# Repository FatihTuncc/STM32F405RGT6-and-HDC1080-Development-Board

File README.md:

# _STM32F405RGT6 and HDC1080 Development Board_

In this project, a development board was designed using the STM32F405RGT6 processor, HDC1080 sensor and MP2359 step-down IC.
> [!NOTE]
> I rendered the PCB 3D file by transferring it to the Blender program and obtained this realistic image.
## _Components_

- **_STM32F405RGT6:_** The STM32F405RGT6 processor is ideal for high-performance embedded system applications with its 168 MHz processing speed and large memory capacity. I also chose this Microprocessor because it is affordable and new generation.

- **_HDC1080:_** The HDC1080 sensor provides high accuracy for temperature and humidity measurements. It works integrated with STM32F405RGT6 to provide accurate and reliable data. It can communicate with I2C Protocol. There may be alternatives instead of this sensor.

- **_MP2359:_** The MP2359 IC has a wide input voltage range. It saves energy with high efficiency Step-Down regulation. It is a well-known and widely used component.

> [!IMPORTANT]
> I designed the circuit design of these components in accordance with the datasheet. I drew the PCB Designs again in accordance with the Datasheet.

## _Components Recommended For Use (JLCPCB)_

- C13738 Crystal Oscillator
- C221841 Boot switch
- C408412 Power Inductor
- C132560 USB Connector

This information is also available in the BOM file.
## _PCB Image_

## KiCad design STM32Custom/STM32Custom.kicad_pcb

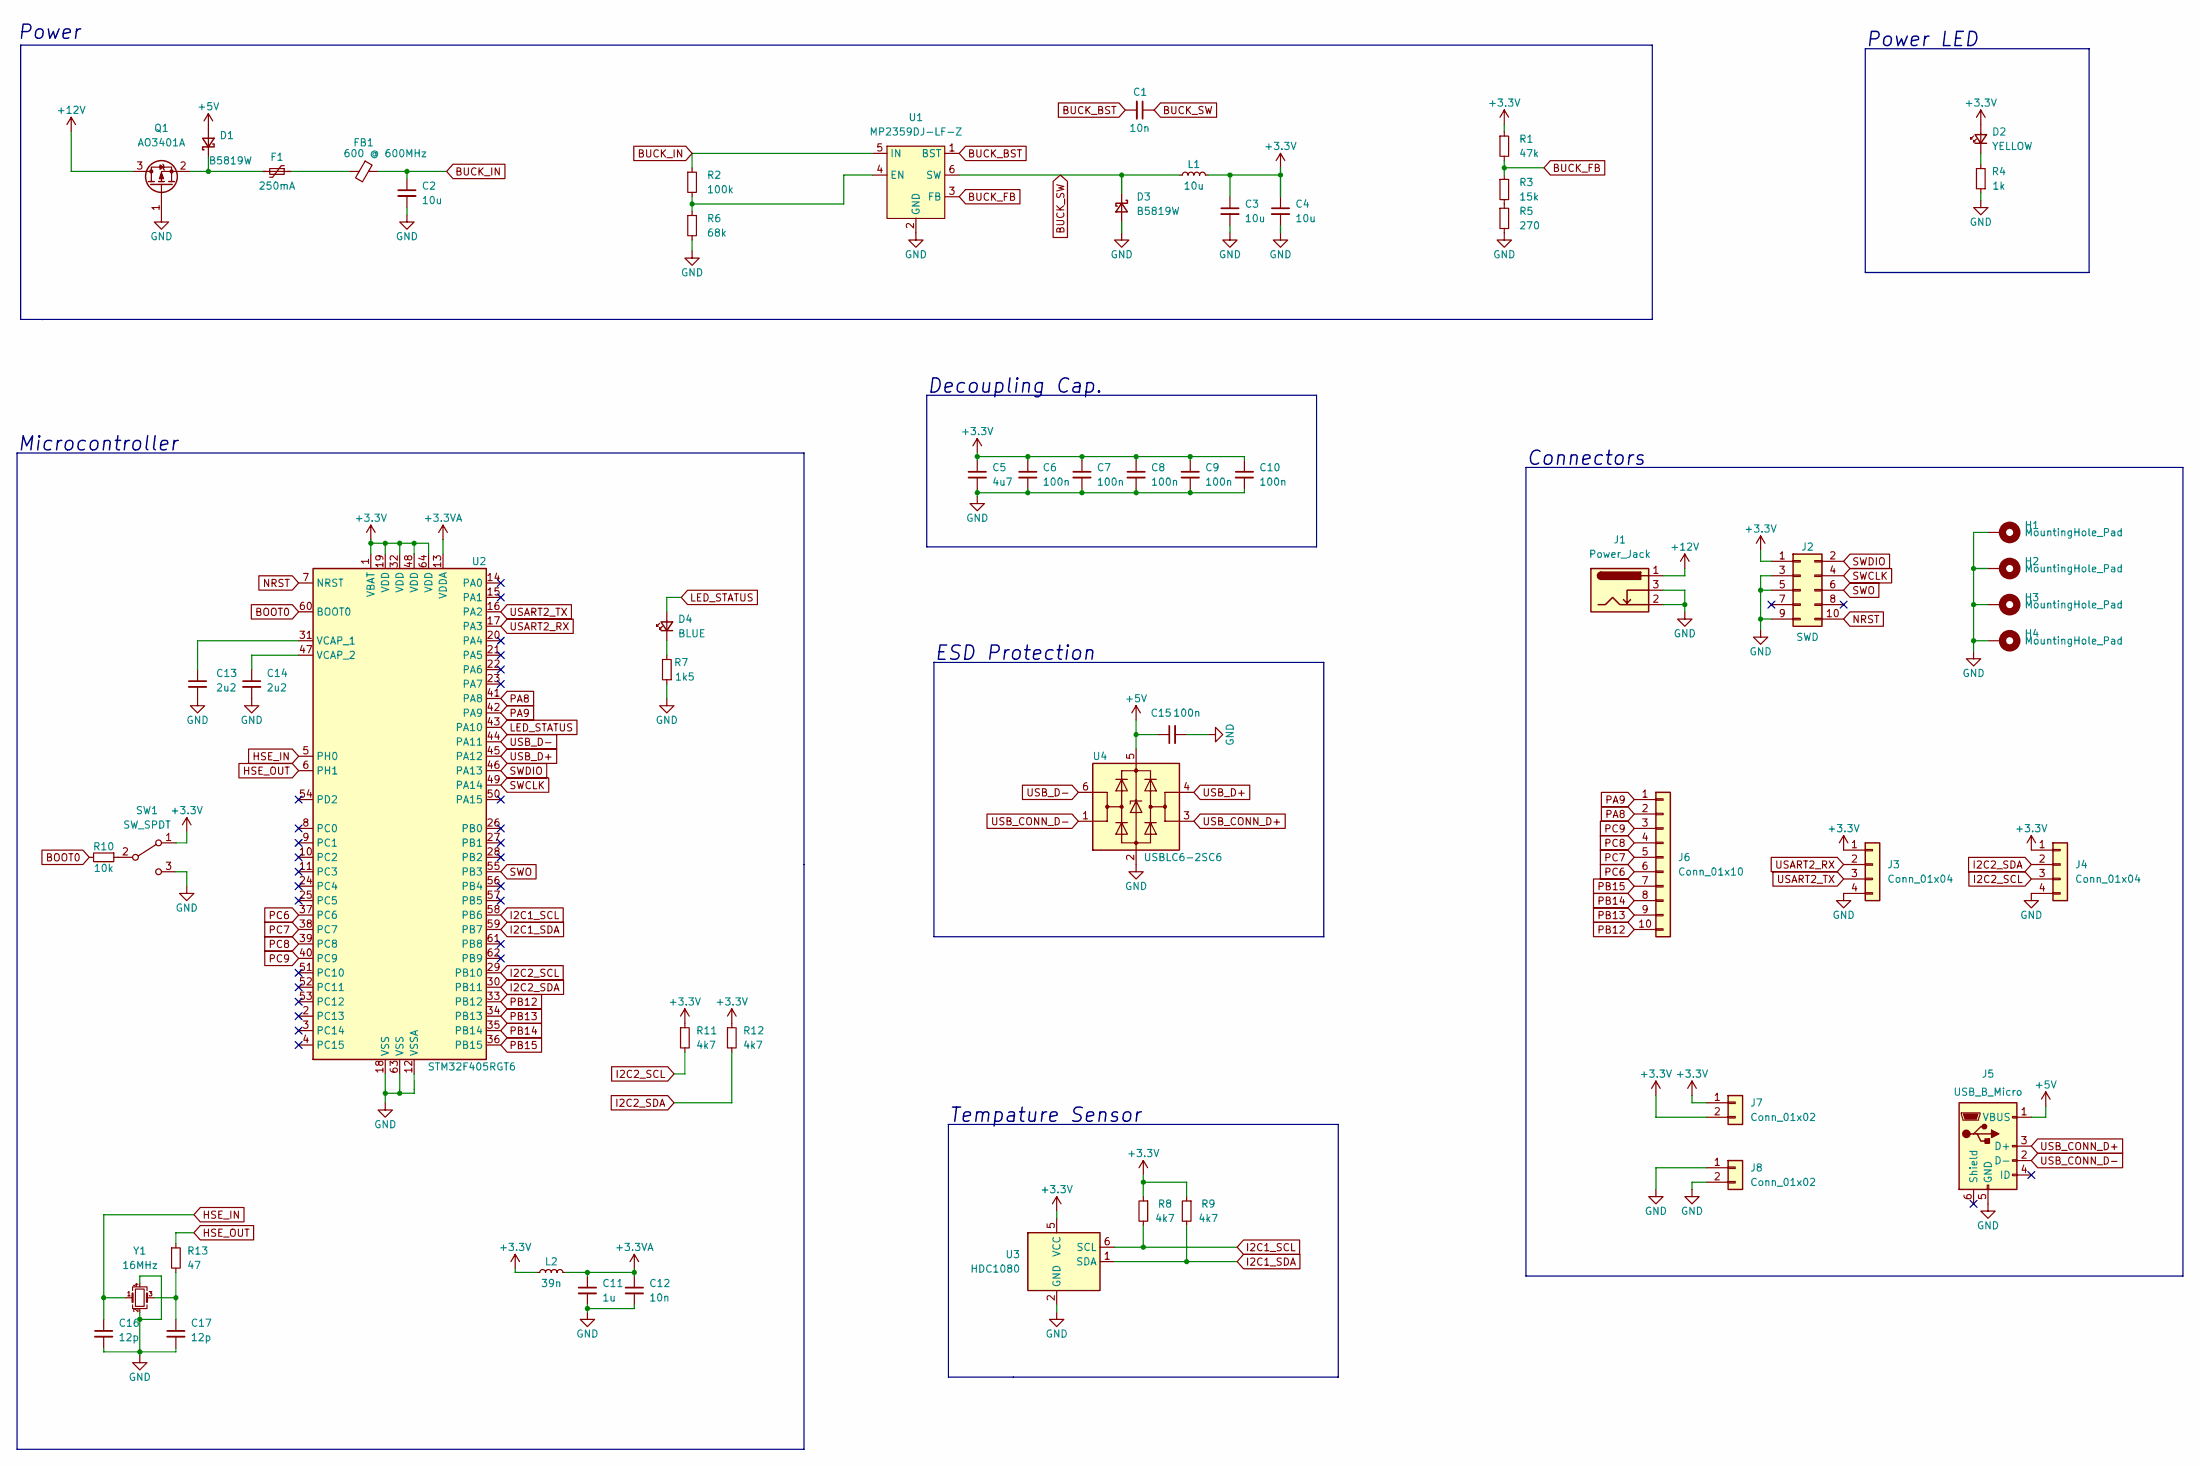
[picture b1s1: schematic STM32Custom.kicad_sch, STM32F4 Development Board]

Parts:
C1: 10n; C_0805_2012Metric; LCSC Part # C1710
C2, C3, C4: 10u; C_1206_3216Metric; LCSC Part # C13585
C5: 4u7; C_0805_2012Metric; LCSC Part # C1779
C6, C7, C8, C9, C10, C15: 100n; C_0603_1608Metric; LCSC Part # C14663
C11: 1u; C_0603_1608Metric; LCSC Part # C15849
C12: 10n; C_0603_1608Metric; LCSC Part # C57112
C13, C14: 2u2; C_0603_1608Metric; LCSC Part # C23630
C16, C17: 12p; C_0603_1608Metric; LCSC Part # C38523
D1, D3: B5819W; D_SOD-123; LCSC Part # C8598
D2: YELLOW; LED_0603_1608Metric; LCSC Part # C72038
D4: BLUE; LED_0603_1608Metric; LCSC Part # C72041
F1: 250mA; Fuse_1206_3216Metric; LCSC Part # C369159
FB1: 600 @ 600MHz; L_0805_2012Metric; LCSC Part # C1017
H1, H2, H3, H4: MountingHole_Pad; MountingHole_4.3mm_M4_Pad_Via
J1: Power_Jack; BarrelJack_Horizontal
J2: SWD; PinHeader_2x05_P2.54mm_Vertical
J3, J4: Conn_01x04; PinHeader_1x04_P2.54mm_Vertical
J5: USB_B_Micro; USB_Micro-B_Molex_47346-0001; LCSC Part # C132560
J6: Conn_01x10; PinHeader_1x10_P2.54mm_Vertical
J7, J8: Conn_01x02; PinHeader_1x02_P2.54mm_Vertical
L1: 10u; L_Sunlord_MWSA05xxS; LCSC Part # C408412
L2: 39n; L_0402_1005Metric; LCSC Part # C26443
Q1: AO3401A; SOT-23; LCSC Part # C15127
R1: 47k; R_0805_2012Metric; LCSC Part # C17713
R2: 100k; R_0805_2012Metric; LCSC Part # C149504
R3: 15k; R_0805_2012Metric; LCSC Part # C17475
R4: 1k; R_0805_2012Metric; LCSC Part # C17513
R5: 270; R_0805_2012Metric; LCSC Part # C17590
R6: 68k; R_0805_2012Metric; LCSC Part # C17801
R7: 1k5; R_0805_2012Metric; LCSC Part # C4310
R8, R9, R11, R12: 4k7; R_0805_2012Metric; LCSC Part # C17673
R10: 10k; R_0805_2012Metric; LCSC Part # C17414
R13: 47; R_0805_2012Metric; LCSC Part # C17714
SW1: SW_SPDT; SW_SPDT_PCM12; LCSC Part # C221841
U1: MP2359DJ-LF-Z; TSOT-23-6; LCSC Part # C2959845
U2: STM32F405RGT6; LQFP-64_10x10mm_P0.5mm; LCSC Part # C15742
U3: HDC1080; Texas_PWSON-N6; LCSC Part # C82227
U4: USBLC6-2SC6; SOT-23-6; LCSC Part # C7519
Y1: 16MHz; Crystal_SMD_3225-4Pin_3.2x2.5mm; LCSC Part # C13738

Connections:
+3.3VA: C11.1, C12.1, L2.2, U2.13 (VDDA)
+3V3: C3.1, C4.1, C5.1, C6.1, C7.1, C8.1, C9.1, C10.1, D2.2 (A), J2.1, J3.1, J4.1, J7.1, J7.2, L1.2, L2.1, R1.1, R8.1, R9.1, R11.1, R12.1, SW1.1 (A), U2.1 (VBAT), U2.19 (VDD), U2.32 (VDD), U2.48 (VDD), U2.64 (VDD), U3.5 (VCC)
+5V: C15.1, D1.2 (A), J5.1 (VBUS), U4.5 (VBUS)
+12V: J1.1, Q1.3 (D)
BOOT0: R10.2, U2.60 (BOOT0)
BUCK_BST: C1.2, U1.1 (BST)
BUCK_FB: R1.2, R3.1, U1.3 (FB)
BUCK_IN: C2.1, FB1.1, R2.1, U1.5 (IN)
BUCK_SW: C1.1, D3.1 (K), L1.1, U1.6 (SW)
GND: C2.2, C3.2, C4.2, C5.2, C6.2, C7.2, C8.2, C9.2, C10.2, C11.2, C12.2, C13.2, C14.2, C15.2, C16.2, C17.2, D3.2 (A), H1.1, H2.1, H3.1, H4.1, J1.2, J1.3, J2.3, J2.5, J2.9, J3.4, J4.4, J5.5 (GND), J8.1, J8.2, Q1.1 (G), R4.1, R5.2, R6.2, R7.1, SW1.3 (C), U1.2 (GND), U2.12 (VSSA), U2.18 (VSS), U2.63 (VSS), U3.2 (GND), U4.2 (GND), Y1.2, Y1.4
HSE_IN: C16.1, U2.5 (PH0), Y1.1
HSE_OUT: R13.1, U2.6 (PH1)
I2C1_SCL: R8.2, U2.58 (PB6), U3.6 (SCL)
I2C1_SDA: R9.2, U2.59 (PB7), U3.1 (SDA)
I2C2_SCL: J4.3, R11.2, U2.29 (PB10)
I2C2_SDA: J4.2, R12.2, U2.30 (PB11)
LED_STATUS: D4.2 (A), U2.43 (PA10)
NRST: J2.10, U2.7 (NRST)
unnamed: C13.1, U2.31 (VCAP_1)
unnamed: C14.1, U2.47 (VCAP_2)
unnamed: C17.1, R13.2, Y1.3
unnamed: D1.1 (K), F1.2, Q1.2 (S)
unnamed: D2.1 (K), R4.2
unnamed: D4.1 (K), R7.2
unnamed: F1.1, FB1.2
unnamed: R2.2, R6.1, U1.4 (EN)
unnamed: R3.2, R5.1
unnamed: R10.1, SW1.2 (B)
PA8: J6.2, U2.41 (PA8)
PA9: J6.1, U2.42 (PA9)
PB12: J6.10, U2.33 (PB12)
PB13: J6.9, U2.34 (PB13)
PB14: J6.8, U2.35 (PB14)
PB15: J6.7, U2.36 (PB15)
PC6: J6.6, U2.37 (PC6)
PC7: J6.5, U2.38 (PC7)
PC8: J6.4, U2.39 (PC8)
PC9: J6.3, U2.40 (PC9)
SWCLK: J2.4, U2.49 (PA14)
SWDIO: J2.2, U2.46 (PA13)
SWO: J2.6, U2.55 (PB3)
USART2_RX: J3.2, U2.17 (PA3)
USART2_TX: J3.3, U2.16 (PA2)
USB_CONN_D+: J5.3 (D+), U4.3 (I/O2)
USB_CONN_D-: J5.2 (D-), U4.1 (I/O1)
USB_D+: U2.45 (PA12), U4.4 (I/O2)
USB_D-: U2.44 (PA11), U4.6 (I/O1)

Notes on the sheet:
ESD Protection
Tempature Sensor
Connectors
Decoupling Cap.
Power
Power LED
Microcontroller

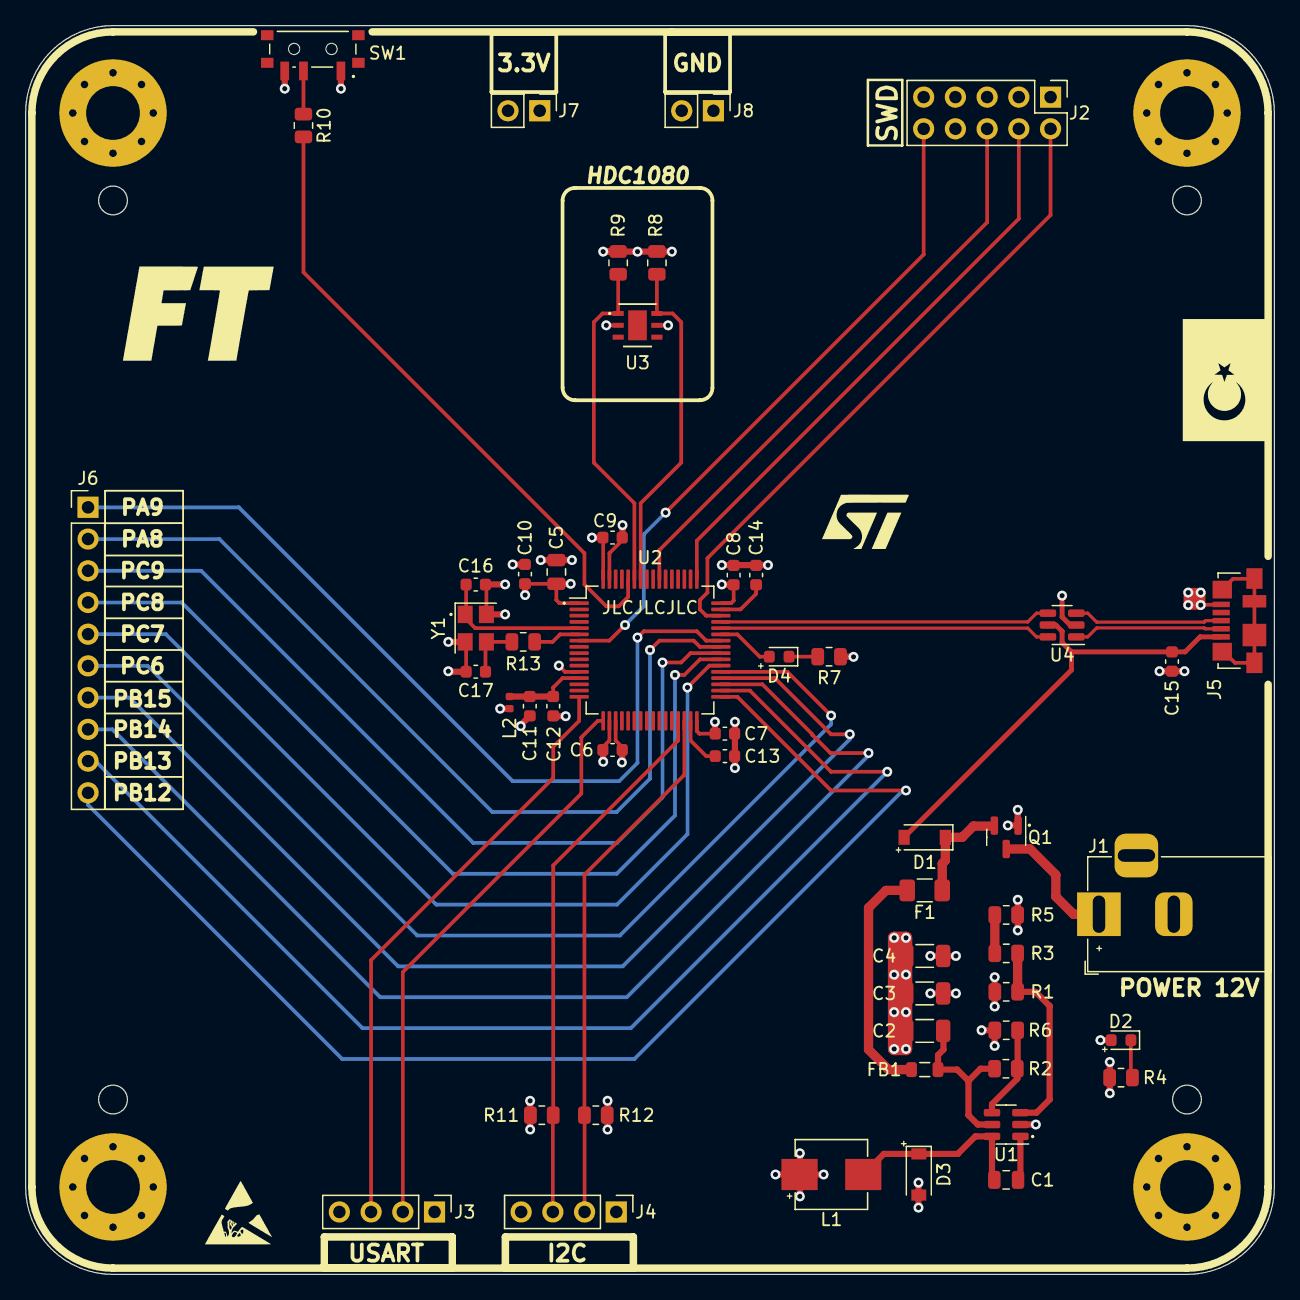
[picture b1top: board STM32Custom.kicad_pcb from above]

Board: 4 copper layers, 100.0 x 100.0 mm, 57 parts (0 on the bottom side), 47 nets.

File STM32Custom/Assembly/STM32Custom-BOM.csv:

Comment,Designator,Footprint,LCSC
"10n","C1","Capacitor_SMD:C_0805_2012Metric","C1710"
"1u","C11","Capacitor_SMD:C_0603_1608Metric","C15849"
"10n","C12","Capacitor_SMD:C_0603_1608Metric","C57112"
"2u2","C13,C14","Capacitor_SMD:C_0603_1608Metric","C23630"
"12p","C16,C17","Capacitor_SMD:C_0603_1608Metric","C38523"
"10u","C2,C3,C4","Capacitor_SMD:C_1206_3216Metric","C13585"
"4u7","C5","Capacitor_SMD:C_0805_2012Metric","C1779"
"100n","C6,C7,C8,C9,C10,C15","Capacitor_SMD:C_0603_1608Metric","C14663"
"B5819W","D1,D3","Diode_SMD:D_SOD-123","C8598"
"YELLOW","D2","LED_SMD:LED_0603_1608Metric","C72038"
"BLUE","D4","LED_SMD:LED_0603_1608Metric","C72041"
"250mA","F1","Fuse:Fuse_1206_3216Metric","C369159"
"600 @ 600MHz","FB1","Inductor_SMD:L_0805_2012Metric","C1017"
"MountingHole_Pad","H1,H2,H3,H4","MountingHole:MountingHole_4.3mm_M4_Pad_Via",""
"Power_Jack","J1","Connector_BarrelJack:BarrelJack_Horizontal",""
"SWD","J2","Connector_PinHeader_2.54mm:PinHeader_2x05_P2.54mm_Vertical",""
"Conn_01x04","J3,J4","Connector_PinHeader_2.54mm:PinHeader_1x04_P2.54mm_Vertical",""
"USB_B_Micro","J5","Connector_USB:USB_Micro-B_Molex_47346-0001","C132560"
"Conn_01x10","J6","Connector_PinHeader_2.54mm:PinHeader_1x10_P2.54mm_Vertical",""
"Conn_01x02","J7,J8","Connector_PinHeader_2.54mm:PinHeader_1x02_P2.54mm_Vertical",""
"10u","L1","Inductor_SMD:L_Sunlord_MWSA05xxS","C408412"
"39n","L2","Inductor_SMD:L_0402_1005Metric","C26443"
"AO3401A","Q1","Package_TO_SOT_SMD:SOT-23","C15127"
"47k","R1","Resistor_SMD:R_0805_2012Metric","C17713"
"10k","R10","Resistor_SMD:R_0805_2012Metric","C17414"
"47","R13","Resistor_SMD:R_0805_2012Metric","C17714"
"100k","R2","Resistor_SMD:R_0805_2012Metric","C149504"
"15k","R3","Resistor_SMD:R_0805_2012Metric","C17475"
"1k","R4","Resistor_SMD:R_0805_2012Metric","C17513"
"270","R5","Resistor_SMD:R_0805_2012Metric","C17590"
"68k","R6","Resistor_SMD:R_0805_2012Metric","C17801"
"1k5","R7","Resistor_SMD:R_0805_2012Metric","C4310"
"4k7","R8,R9,R11,R12","Resistor_SMD:R_0805_2012Metric","C17673"
"SW_SPDT","SW1","Button_Switch_SMD:SW_SPDT_PCM12","C221841"
"MP2359DJ-LF-Z","U1","Package_TO_SOT_SMD:TSOT-23-6","C2959845"
"STM32F405RGT6","U2","Package_QFP:LQFP-64_10x10mm_P0.5mm","C15742"
"HDC1080","U3","Package_SON:Texas_PWSON-N6","C82227"
"USBLC6-2SC6","U4","Package_TO_SOT_SMD:SOT-23-6","C7519"
"16MHz","Y1","Crystal:Crystal_SMD_3225-4Pin_3.2x2.5mm","C13738"

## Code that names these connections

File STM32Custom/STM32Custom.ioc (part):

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Mcu.Name=STM32F405RGTx
Mcu.Package=LQFP64
Mcu.UserName=STM32F405RGTx
PA10.Signal=GPIO_Output
PA11.Mode=Device_Only
PA11.Signal=USB_OTG_FS_DM
PA12.Mode=Device_Only
PA12.Signal=USB_OTG_FS_DP
PA13.Mode=Trace_Asynchronous_SW
PA13.Signal=SYS_JTMS-SWDIO
PA14.Mode=Trace_Asynchronous_SW
PA14.Signal=SYS_JTCK-SWCLK
PA2.Mode=Asynchronous
PA2.Signal=USART2_TX
PA3.Mode=Asynchronous
PA3.Signal=USART2_RX
PB10.Mode=I2C
PB10.Signal=I2C2_SCL
PB11.Mode=I2C
PB11.Signal=I2C2_SDA
PB3.Mode=Trace_Asynchronous_SW
PB3.Signal=SYS_JTDO-SWO
PB6.Mode=I2C
PB6.Signal=I2C1_SCL
PB7.Mode=I2C
PB7.Signal=I2C1_SDA
PH0-OSC_IN.Mode=HSE-External-Oscillator
PH0-OSC_IN.Signal=RCC_OSC_IN
PH1-OSC_OUT.Mode=HSE-External-Oscillator
PH1-OSC_OUT.Signal=RCC_OSC_OUT
RCC.HSE_VALUE=25000000
RCC.SYSCLKFreq_VALUE=16000000
board=custom

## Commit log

2023-08-14 Deleted past commits
